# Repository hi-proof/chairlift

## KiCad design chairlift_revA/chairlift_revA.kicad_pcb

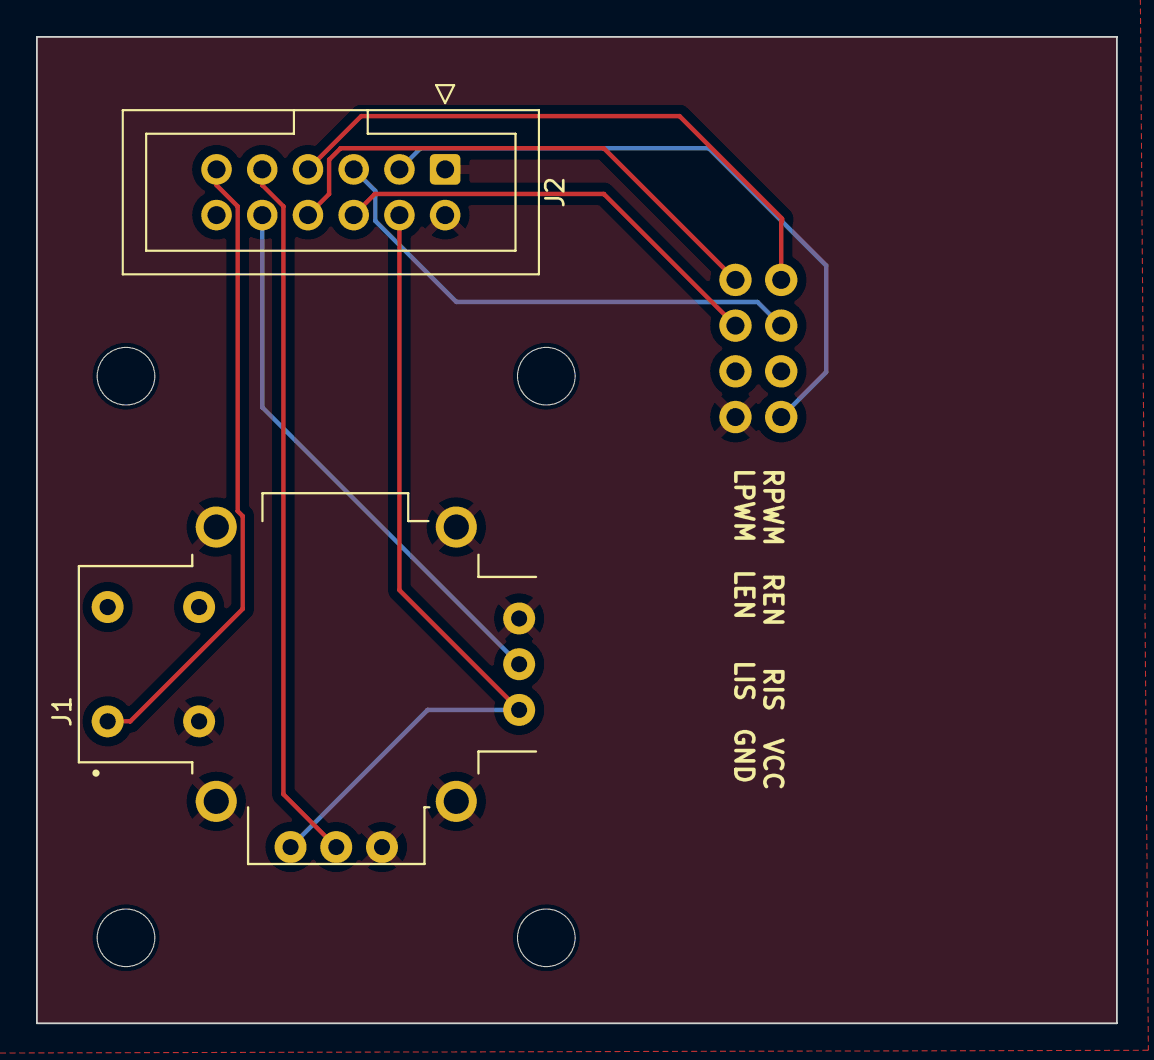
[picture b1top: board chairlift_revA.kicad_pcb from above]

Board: 2 copper layers, 60.0 x 54.8 mm, 3 parts (1 on the bottom side), 10 nets.

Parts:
J1: COM-09032; XDCR_COM-09032
J2: Conn_02x06_Odd_Even; IDC-Header_2x06_P2.54mm_Vertical
U1: BTS7960_Module

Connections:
+3V3: J1.H1 (H+), J1.V1 (V+), J2.4
+5V: J2.3, U1.7 (VCC)
D1: J2.5, U1.3 (R_EN)
D2: J2.6, U1.4 (L_EN)
D3: J2.7, U1.1 (RPWM)
D4: J2.8, U1.2 (LPWM)
D5: J1.V2 (V), J2.9
D6: J1.H2 (H), J2.10
D7: J1.B1A (SEL+), J2.11
GND: J1.B2A (SEL-), J1.H3 (H-), J1.S1 (SHIELD), J1.S2 (SHIELD), J1.S3 (SHIELD), J1.S4 (SHIELD), J1.V3 (V-), J2.1, J2.2, U1.8 (GND)
